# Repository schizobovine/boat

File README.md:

Battery Operated Arduino Thermometer (B.O.A.T.)
==============

Similar to Moteino/Anarduino, an Arduino-compatiblish uC board with onboard
RFM69CW, SMA edge connector, and i2c thermometer chip. Powered by CR2032
batter. No onboard voltage regulation, so don't plug into 5V unless you need a
doorstop (the ATMega will be fine, but the wireless card and thermometer are
only specced for 3.6V max).

Yes, there are many Arduino-based wireless sensor projects out there. Most use
2.4GHz radios, however, and that's getting to be an awful crowded band,
especially if one lives in an apartment building. To avoid making that even
worse, I choose to use one of the other ISM bands, specifically 433MHz. This is
normally used for stuff like garage door openers and the like. (Also military
radar, which makes for some hilarious anecdotes).

Anyway, I decided to build my own board for this, even if other designs exist
that are probably better in just about every way. But this one is my own
special snowflake. It even has a cow on it! (Don't judge me.)

Licensed under the Creative Commons Attribution-ShareAlike License
(CC-BY-SA-4.0)

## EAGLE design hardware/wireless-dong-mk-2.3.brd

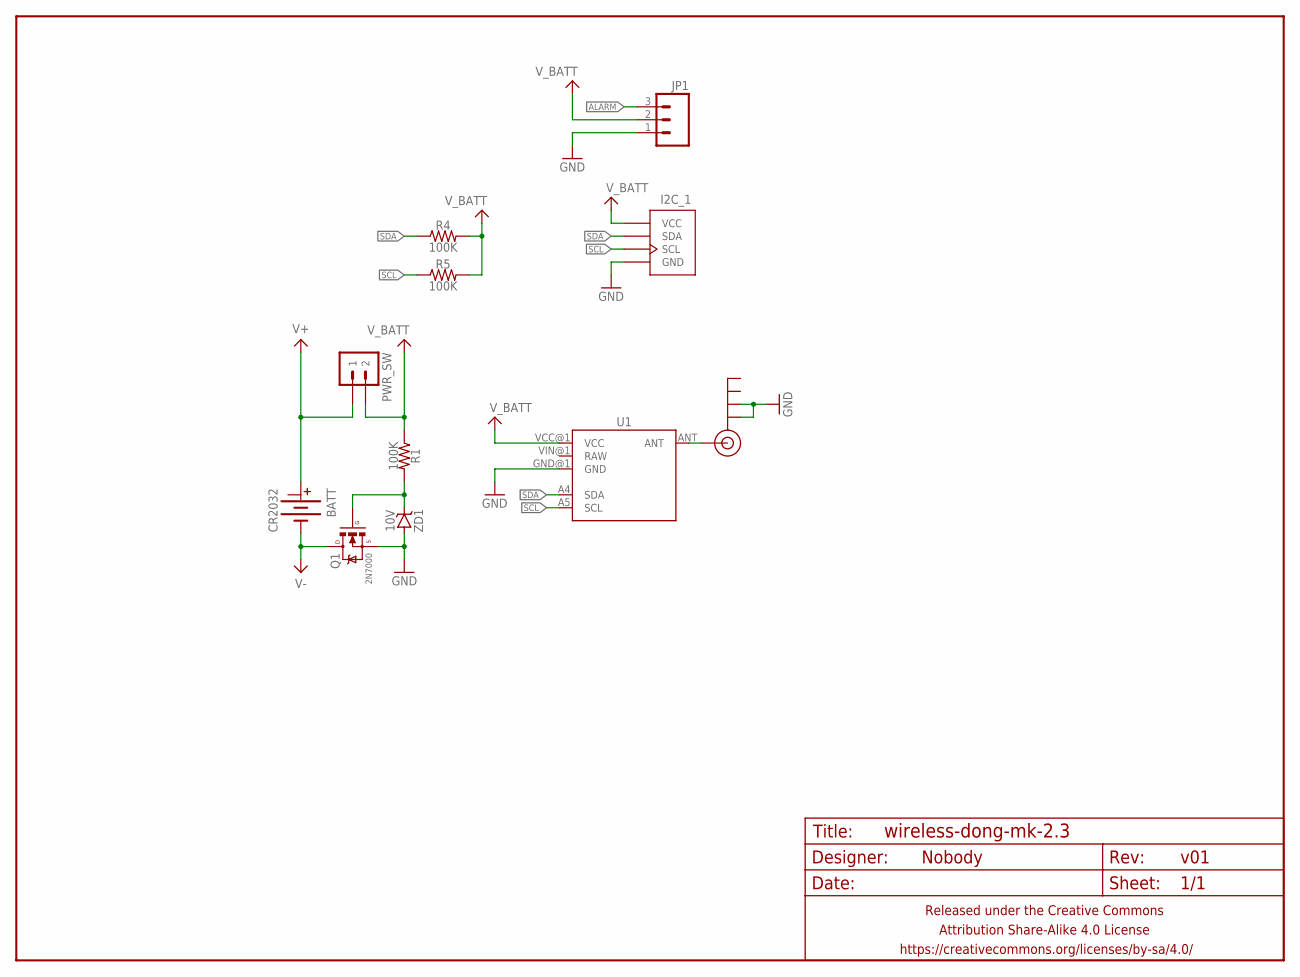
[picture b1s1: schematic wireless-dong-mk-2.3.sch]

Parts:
ANT: SMA_EDGE; SMA-EDGE
BATT: CR2032; BATTCON_20MM_MINE_STAHPIT
FRAME1: FRAME-LETTERNO_PACKAGE; DUMMY
I2C_1: M04-I2CJST-4-PH-RA-CENTERED; 1X04-JST-PH-RA-PTH-I2C-CENTERED
JP1: M03JST-PTH; JST-3-PH-RA-PTH
PWR_SW: M02PTH-CENTERED; 1X02-CENTER
Q1: 2N7000; SOT23
R1, R4, R5: 100K; R0805
U1: MOTEINO_BOAT
ZD1: 10V; SOT23

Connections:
ALARM: JP1.3
GND: ANT.GND@0 (GND), ANT.GND@1 (GND), I2C_1.1 (GND), JP1.1, Q1.2 (S), U1.GND@1 (GND), ZD1.1 (A), ZD1.2 (A)
unnamed: Q1.1 (G), R1.2, ZD1.3 (C)
unnamed: ANT.SIG (SIGNAL), U1.ANT
SCL: I2C_1.4 (SCL), R5.1, U1.A5 (SCL)
SDA: I2C_1.3 (SDA), R4.1, U1.A4 (SDA)
V+: BATT.TOP@1 (+), PWR_SW.1
V-: BATT.BOTTOM (-), Q1.3 (D)
V_BATT: I2C_1.2 (VCC), JP1.2, PWR_SW.2, R1.1, R4.2, R5.2, U1.VCC@1 (VCC)

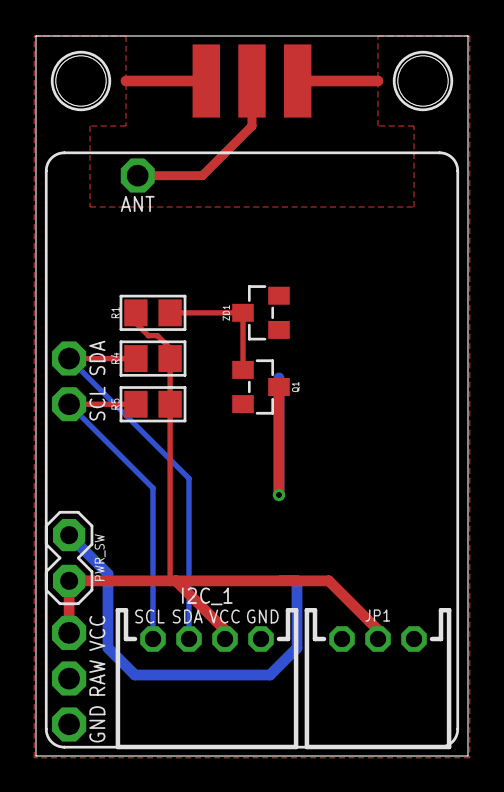
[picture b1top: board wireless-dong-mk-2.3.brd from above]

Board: 2 copper layers, 24.0 x 40.0 mm, 12 parts (1 on the bottom side), 8 nets.

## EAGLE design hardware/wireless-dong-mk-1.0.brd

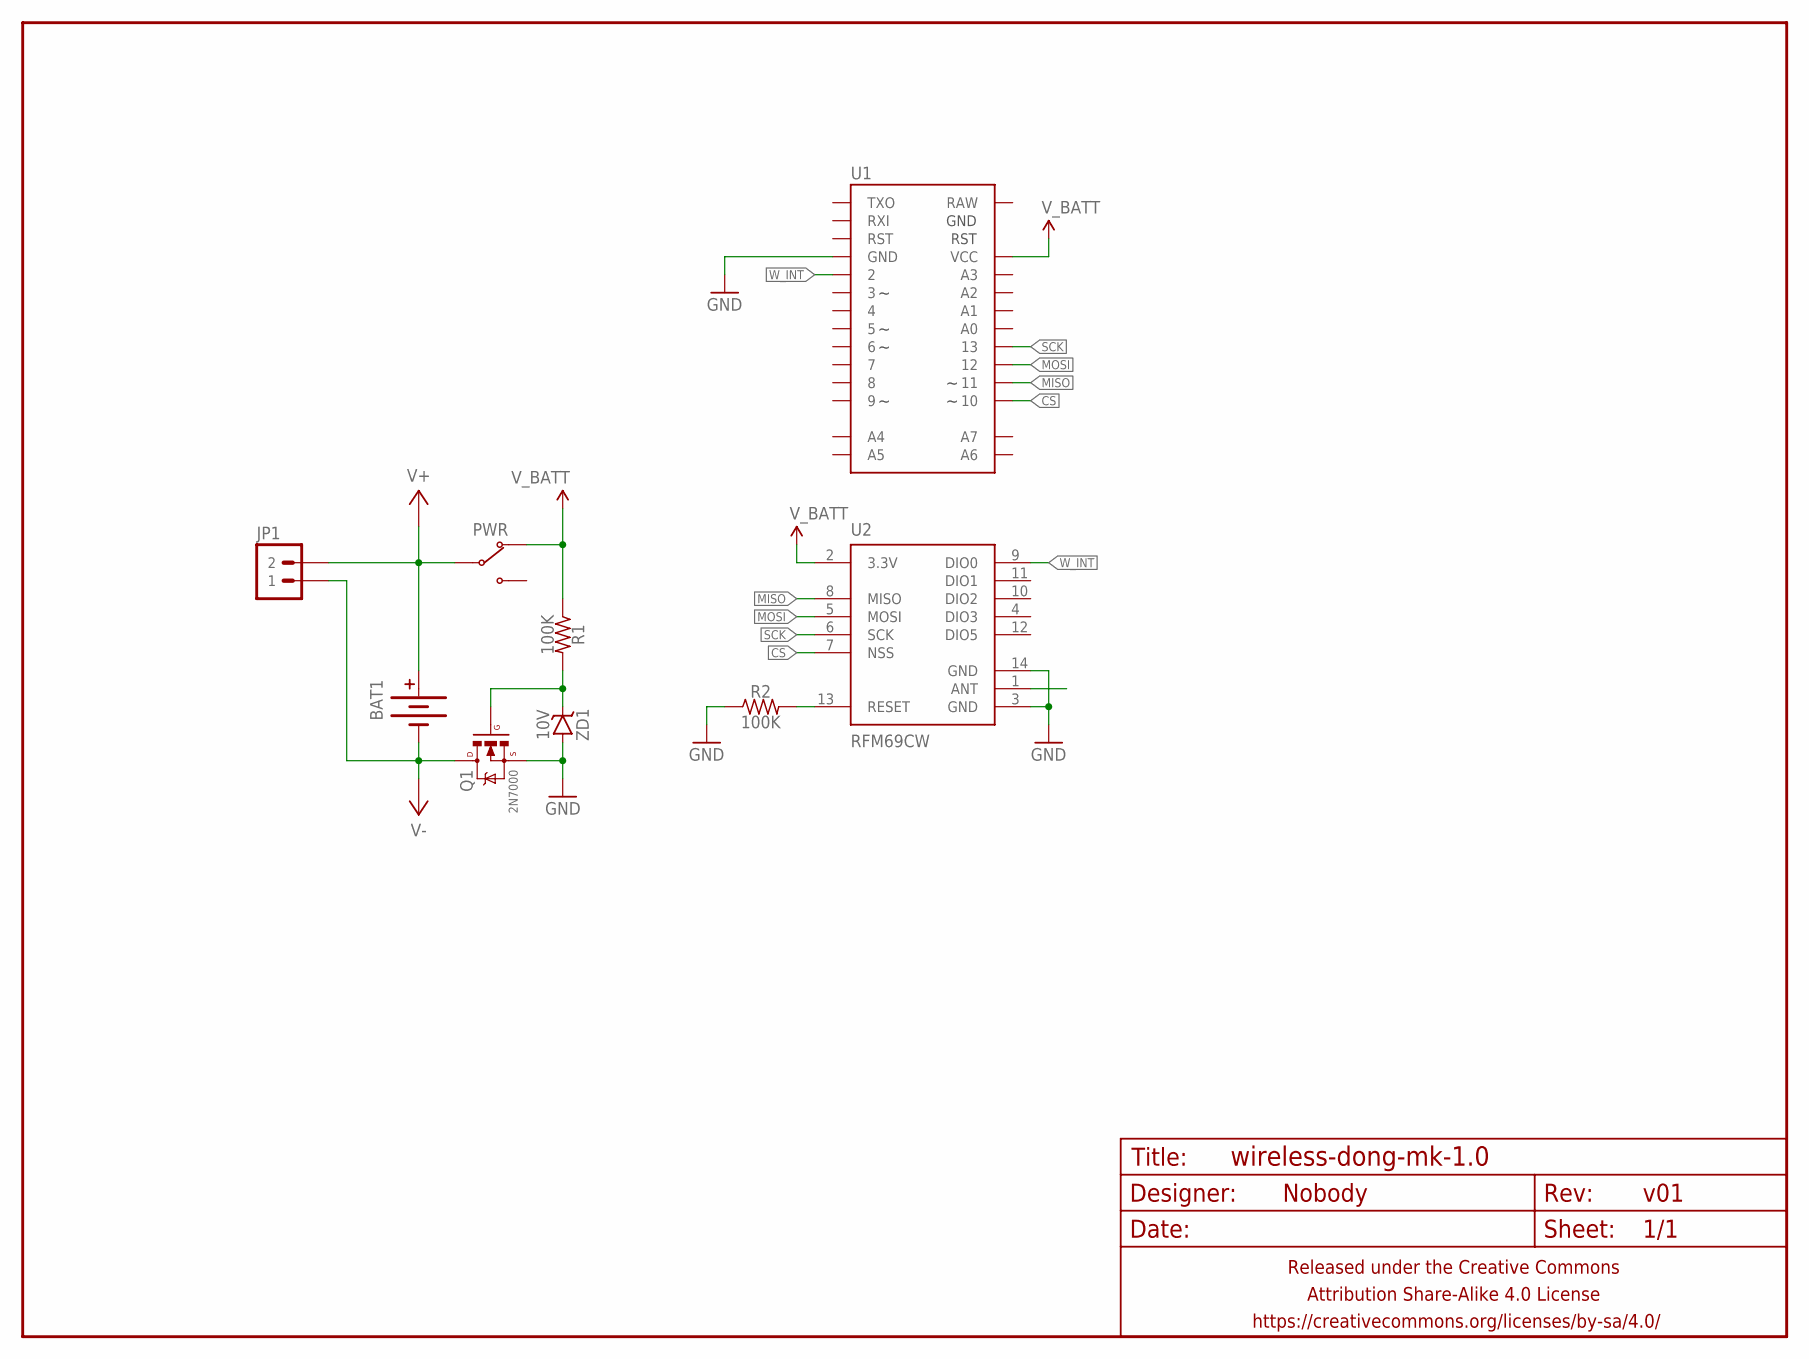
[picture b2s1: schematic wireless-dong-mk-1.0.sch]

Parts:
BAT1: BATTERYAA; BATTERY-AA
FRAME1: FRAME-LETTERNO_PACKAGE; DUMMY
JP1: M02PTH-CENTERED-R+; 1X02-CENTER-R+
PWR: SWITCH-SPDTPTH-RA-2.54MM; SPDT-RA-2.54MM
Q1: 2N7000; SOT23
R1, R2: 100K; R0603
U1: ARDUINO-PRO-MINI-NO-FTDIARDUINO_PRO_MINI_NO_FTDI_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; ARDUINO_PRO_MINI_NO_FTDI_NO_SILK
U2: RFM69CW; RFM69CW-XXXS2
ZD1: 10V; SOT23

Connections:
CS: U1.10, U2.7 (NSS)
GND: Q1.2 (S), R2.1, U1.GND@1 (GND), U1.GND@2 (GND), U2.3 (GND), U2.14 (GND), ZD1.1 (A), ZD1.2 (A)
MISO: U1.11, U2.8 (MISO)
MOSI: U1.12, U2.5 (MOSI)
unnamed: Q1.1 (G), R1.2, ZD1.3 (C)
unnamed: R2.2, U2.13 (RESET)
SCK: U1.13, U2.6 (SCK)
V+: BAT1.PWR@1 (+), BAT1.PWR@2 (+), JP1.2, PWR.2 (COM)
V-: BAT1.GND@1 (-), BAT1.GND@2 (-), JP1.1, Q1.3 (D)
V_BATT: PWR.1 (NC), R1.1, U1.VCC, U2.2 (3.3V)
W_INT: U1.2, U2.9 (DIO0)

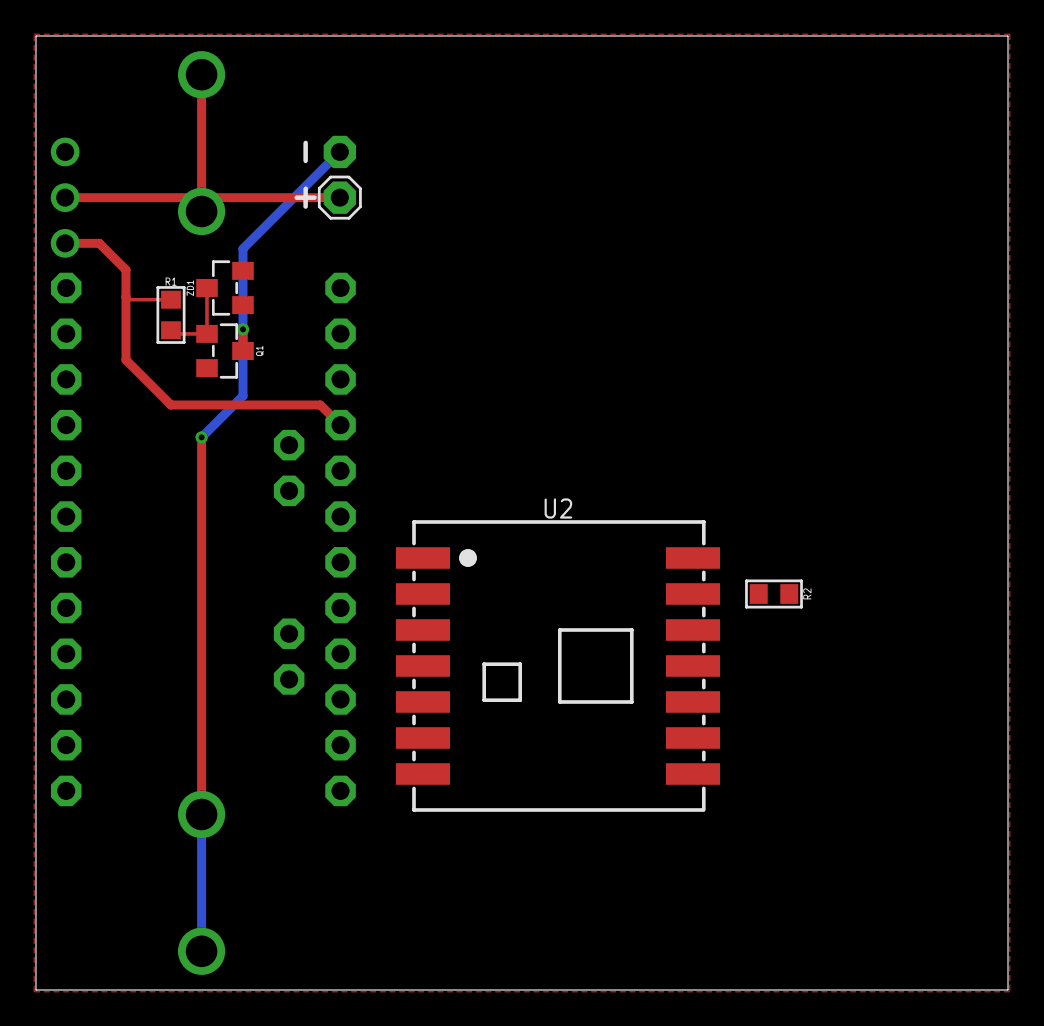
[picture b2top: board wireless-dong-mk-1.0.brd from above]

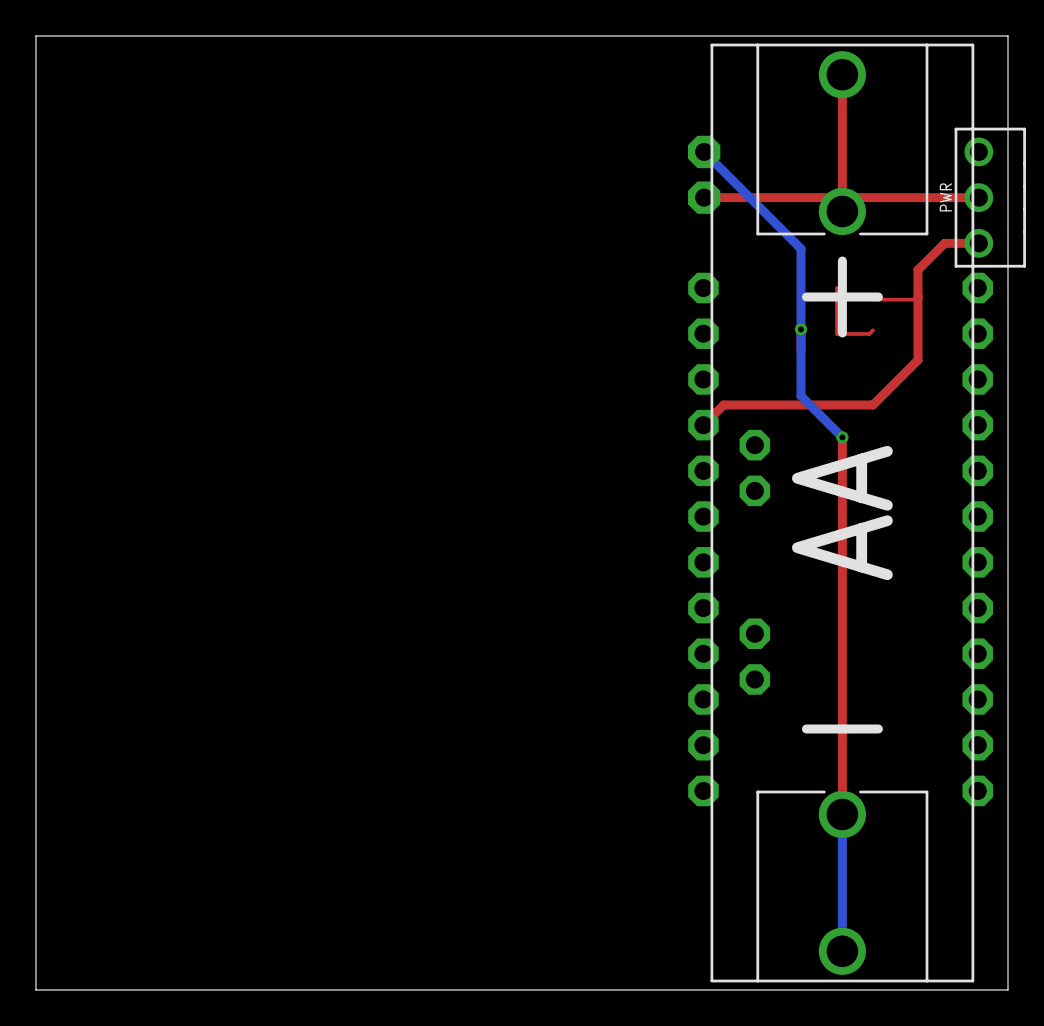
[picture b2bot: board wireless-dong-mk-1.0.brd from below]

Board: 2 copper layers, 54.0 x 53.0 mm, 10 parts (2 on the bottom side), 11 nets.

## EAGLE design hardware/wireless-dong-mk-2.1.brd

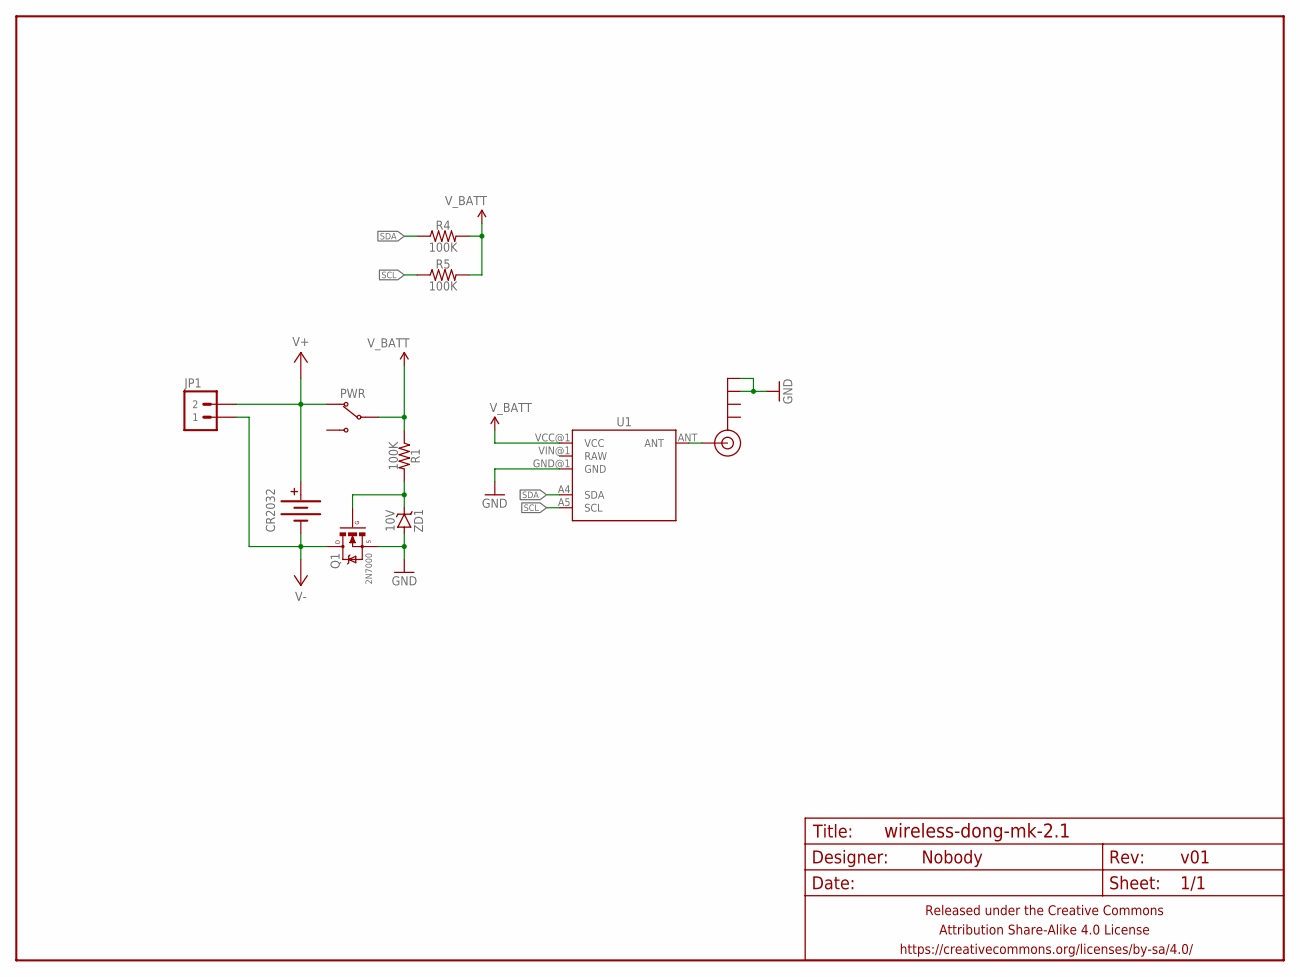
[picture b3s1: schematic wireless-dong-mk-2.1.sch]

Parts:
ANT: SMA_EDGE; SMA-EDGE
CR2032: BATTERY20PTH_TOPLOAD; BATTCON_20MM_PTH_TOPLOAD
FRAME1: FRAME-LETTERNO_PACKAGE; DUMMY
JP1: M02PTH-CENTERED-R+; 1X02-CENTER-R+
PWR: SWITCH-SPDTPTH-RA-2.54MM; SPDT-RA-2.54MM
Q1: 2N7000; SOT23
R1, R4, R5: 100K; R0603
U1: MOTEINO_BOAT
ZD1: 10V; SOT23

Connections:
GND: ANT.GND@2 (GND), ANT.GND@3 (GND), Q1.2 (S), U1.GND@1 (GND), ZD1.1 (A), ZD1.2 (A)
unnamed: Q1.1 (G), R1.2, ZD1.3 (C)
unnamed: ANT.SIG (SIGNAL), U1.ANT
SCL: R5.1, U1.A5 (SCL)
SDA: R4.1, U1.A4 (SDA)
V+: CR2032.+, JP1.2, PWR.1 (NC)
V-: CR2032.-, JP1.1, Q1.3 (D)
V_BATT: PWR.2 (COM), R1.1, R4.2, R5.2, U1.VCC@1 (VCC)

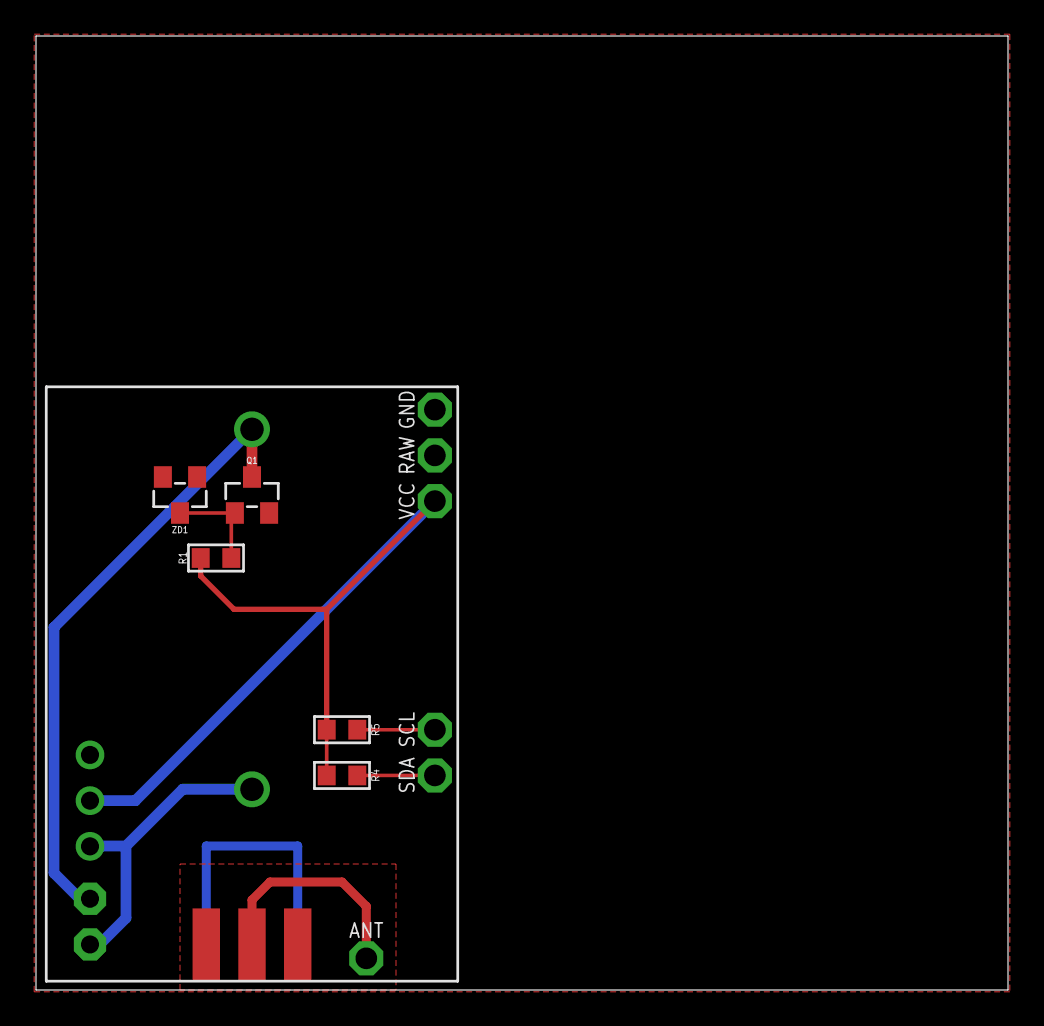
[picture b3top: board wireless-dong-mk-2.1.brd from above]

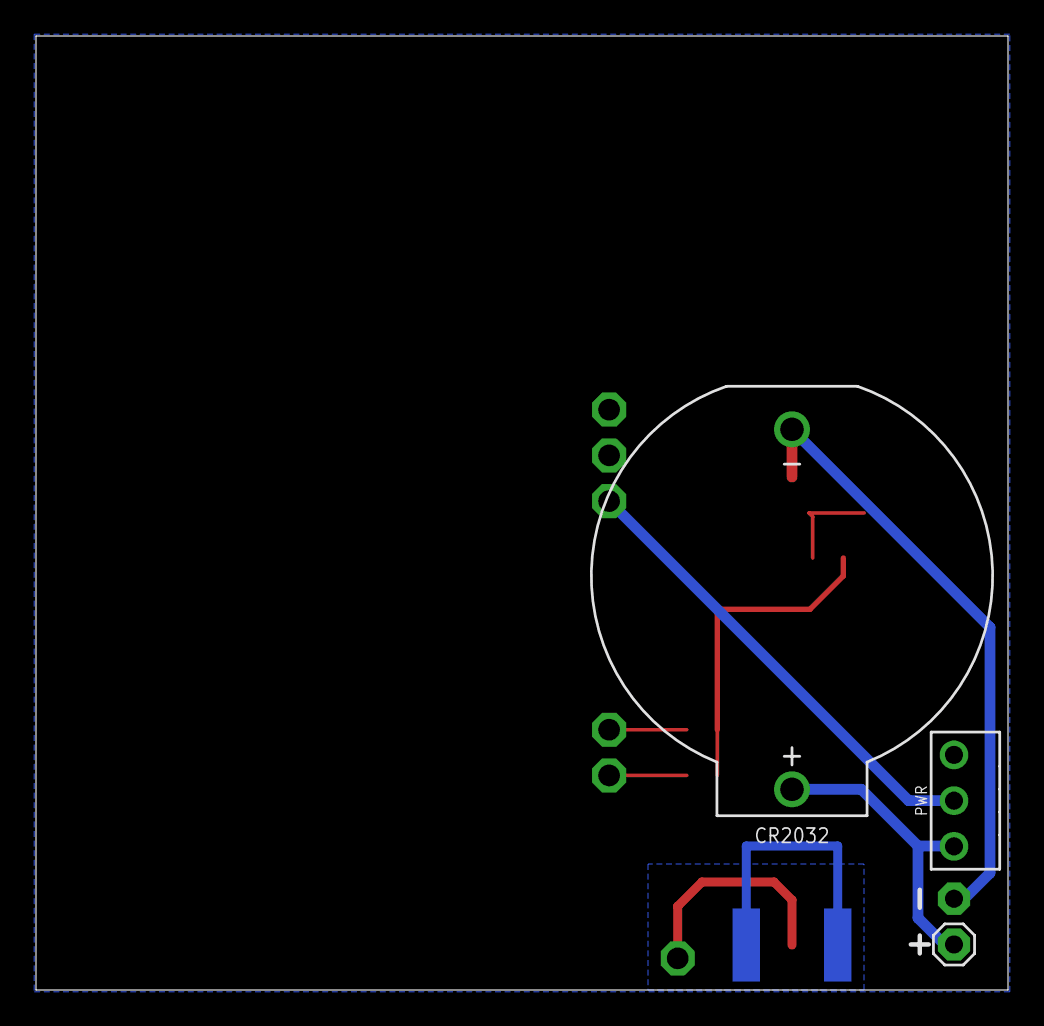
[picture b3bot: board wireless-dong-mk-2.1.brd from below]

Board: 2 copper layers, 54.0 x 53.0 mm, 11 parts (3 on the bottom side), 8 nets.

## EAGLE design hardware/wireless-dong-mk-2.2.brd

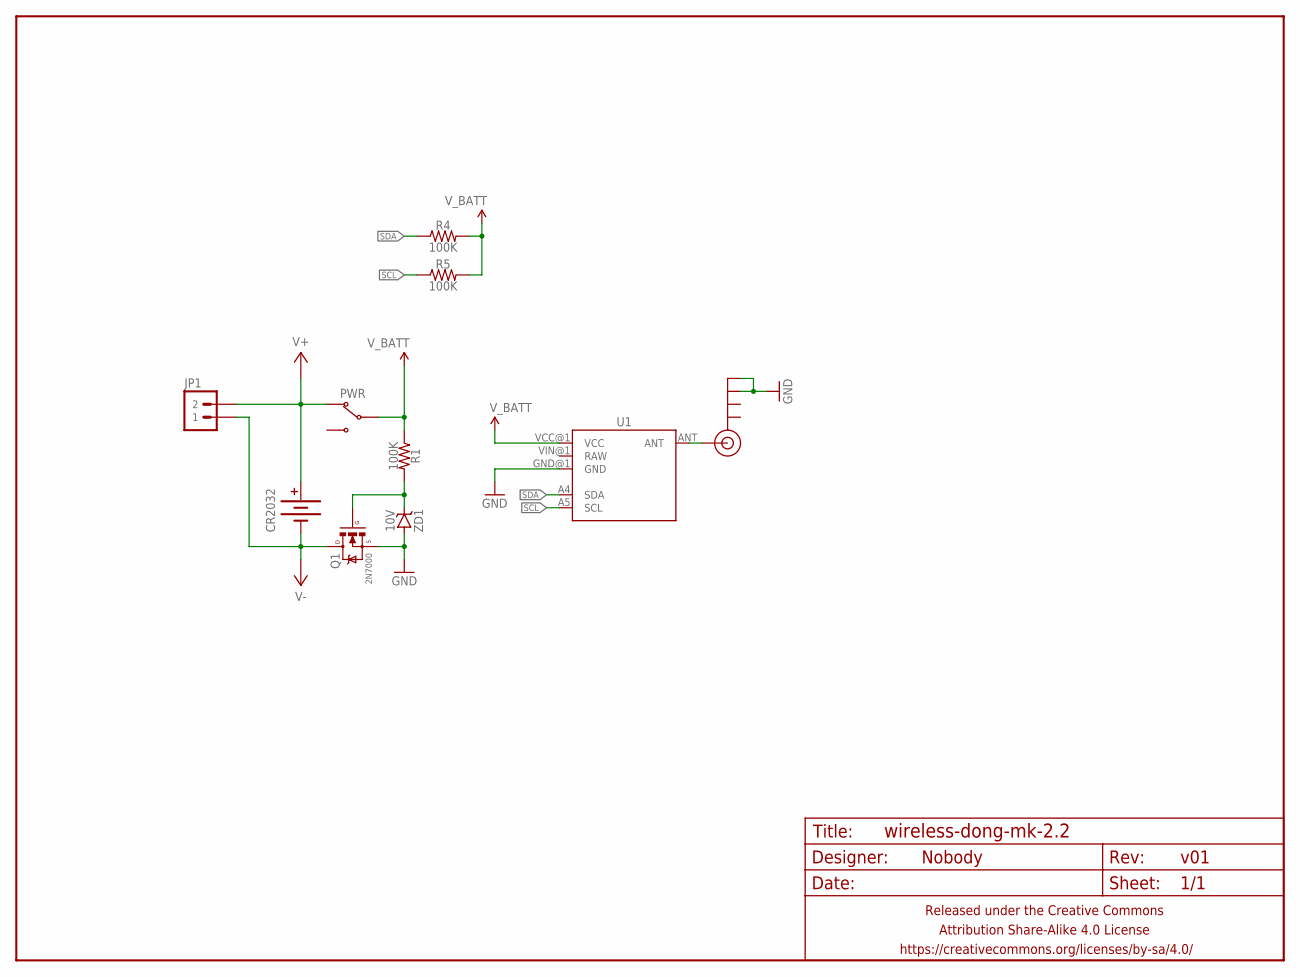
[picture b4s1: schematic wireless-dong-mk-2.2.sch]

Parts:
ANT: SMA_EDGE; SMA-EDGE
CR2032: BATTERY20PTH_TOPLOAD; BATTCON_20MM_PTH_TOPLOAD
FRAME1: FRAME-LETTERNO_PACKAGE; DUMMY
JP1: M02PTH-CENTERED-R+; 1X02-CENTER-R+
PWR: SWITCH-SPDTPTH-RA-2.54MM; SPDT-RA-2.54MM
Q1: 2N7000; TO-92-AMMO
R1, R4, R5: 100K; RESISTOR-AXIAL-PTH-7.62MM
U1: MOTEINO_BOAT
ZD1: 10V; DIODE-ZENNER-7.62MM

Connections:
GND: ANT.GND@2 (GND), ANT.GND@3 (GND), Q1.1 (S), U1.GND@1 (GND), ZD1.A
unnamed: Q1.2 (G), R1.P$2 (2), ZD1.K (C)
unnamed: ANT.SIG (SIGNAL), U1.ANT
SCL: R5.P$1 (1), U1.A5 (SCL)
SDA: R4.P$1 (1), U1.A4 (SDA)
V+: CR2032.+, JP1.2, PWR.1 (NC)
V-: CR2032.-, JP1.1, Q1.3 (D)
V_BATT: PWR.2 (COM), R1.P$1 (1), R4.P$2 (2), R5.P$2 (2), U1.VCC@1 (VCC)

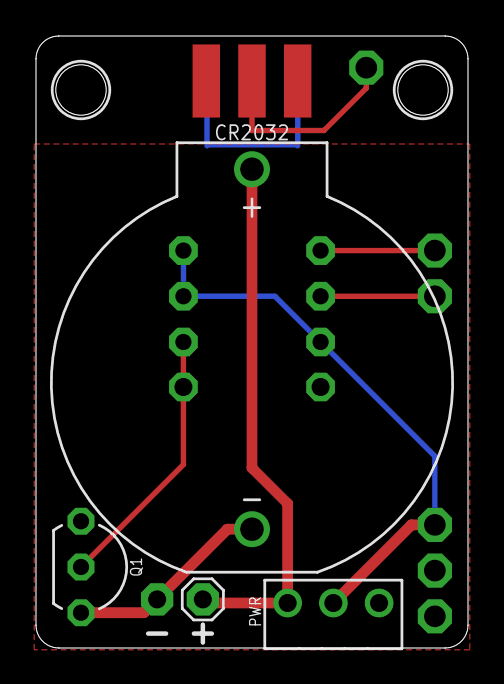
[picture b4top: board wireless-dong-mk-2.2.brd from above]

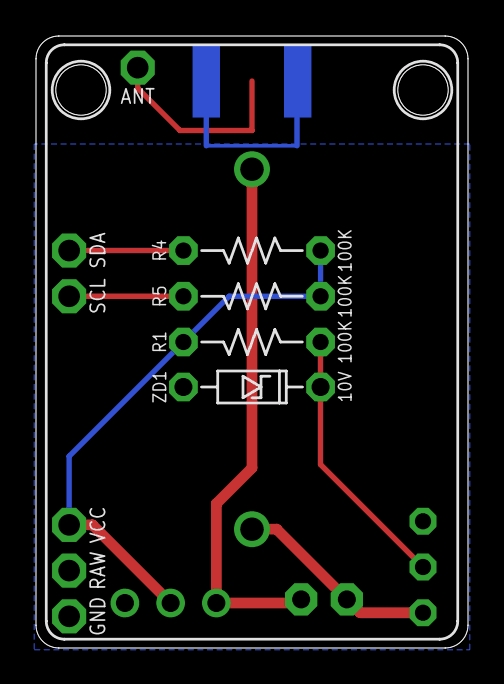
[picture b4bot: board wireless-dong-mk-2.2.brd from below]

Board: 2 copper layers, 24.0 x 34.0 mm, 11 parts (5 on the bottom side), 8 nets.

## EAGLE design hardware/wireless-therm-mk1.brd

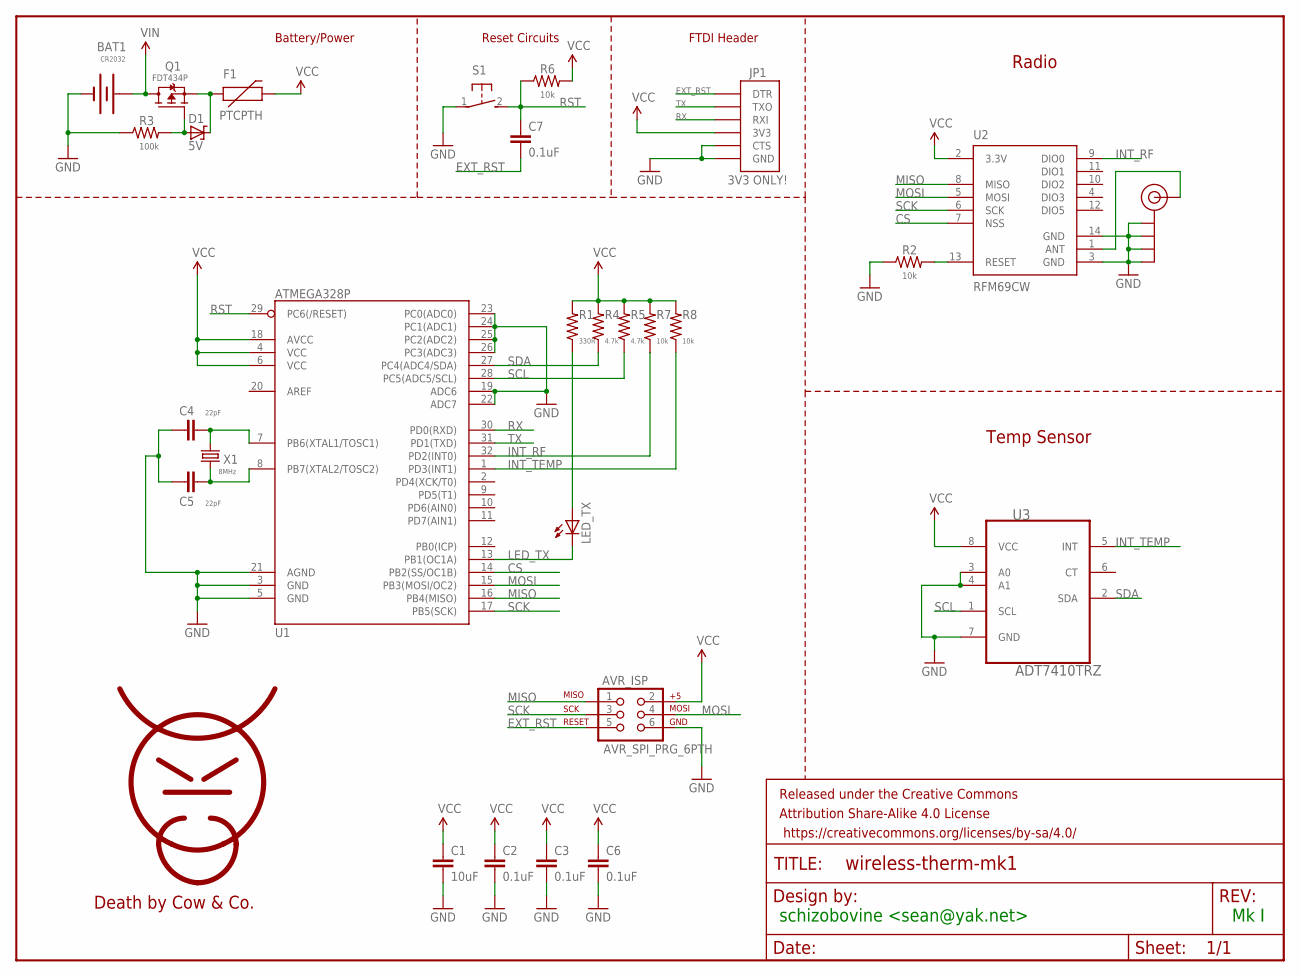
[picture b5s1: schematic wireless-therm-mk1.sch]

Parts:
AVR_ISP: AVR_SPI_PRG_6PTH; 2X3
BAT1: CR2032; BATTCON_20MM
C1: 10uF; C050-025X075
C2, C3, C6, C7: 0.1uF; C025-024X044
C4, C5: 22pF; C025-025X050
D1: 5V; DO34Z7
F1: PTCPTH; PTC
FRAME1: FRAME-LETTER; CREATIVE_COMMONS
JP1: 3V3 ONLY!; FTDI_3V3
LED_TX: GREEN; LED3MM
Q1: FDT434P; SOT223
R1: 330R; 0204/5
R2, R6, R7, R8: 10k; 0204/5
R3: 100k; 0204/5
R4, R5: 4.7k; 0204/5
S1: DTS-3
SMA_CON: SMA_EDGE; SMA-EDGE
U1: ATMEGA328P; TQFP32-08
U2: RFM69CW; RFM69CW-XXXS2
U3: ADT7410TRZ; SOIC127P600X175-8N
U$4: COW
X1: 8MHz; HC49U70

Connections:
ANT: SMA_CON.SIG (SIGNAL), U2.1 (ANT)
CS: U1.14 (PB2(SS/OC1B)), U2.7 (NSS)
EXT_RST: AVR_ISP.5, C7.2, JP1.P$1 (DTR)
GND: AVR_ISP.6, BAT1.2 (-), C1.2, C2.2, C3.2, C4.1, C5.1, C6.2, JP1.P$5 (CTS), JP1.P$6 (GND), R2.1, R3.1, S1.1, SMA_CON.GND@0 (GND), SMA_CON.GND@1 (GND), SMA_CON.GND@2 (GND), SMA_CON.GND@3 (GND), U1.3 (GND), U1.5 (GND), U1.19 (ADC6), U1.21 (AGND), U1.22 (ADC7), U1.23 (PC0(ADC0)), U1.24 (PC1(ADC1)), U1.25 (PC2(ADC2)), U1.26 (PC3(ADC3)), U2.3 (GND), U2.14 (GND), U3.3 (A0), U3.4 (A1), U3.7 (GND)
INT_RF: R7.1, U1.32 (PD2(INT0)), U2.9 (DIO0)
INT_TEMP: R8.1, U1.1 (PD3(INT1)), U3.5 (INT)
LED_TX: LED_TX.K (C), U1.13 (PB1(OC1A))
MISO: AVR_ISP.1, U1.16 (PB4(MISO)), U2.8 (MISO)
MOSI: AVR_ISP.4, U1.15 (PB3(MOSI/OC2)), U2.5 (MOSI)
unnamed: LED_TX.A, R1.1
unnamed: R2.2, U2.13 (RESET)
unnamed: D1.C, F1.P$1 (1), Q1.3 (S)
unnamed: C4.2, U1.7 (PB6(XTAL1/TOSC1)), X1.2
unnamed: C5.2, U1.8 (PB7(XTAL2/TOSC2)), X1.1
unnamed: D1.A, Q1.1 (G), R3.2
RST: C7.1, R6.1, S1.2, U1.29 (PC6(/RESET))
RX: JP1.P$3 (RXI), U1.30 (PD0(RXD))
SCK: AVR_ISP.3, U1.17 (PB5(SCK)), U2.6 (SCK)
SCL: R5.1, U1.28 (PC5(ADC5/SCL)), U3.1 (SCL)
SDA: R4.1, U1.27 (PC4(ADC4/SDA)), U3.2 (SDA)
TX: JP1.P$2 (TXO), U1.31 (PD1(TXD))
VCC: AVR_ISP.2, C1.1, C2.1, C3.1, C6.1, F1.P$2 (2), JP1.P$4 (3V3), R1.2, R4.2, R5.2, R6.2, R7.2, R8.2, U1.4 (VCC), U1.6 (VCC), U1.18 (AVCC), U2.2 (3.3V), U3.8 (VCC)
VIN: BAT1.1 (+), BAT1.3 (+), Q1.2 (D), Q1.4 (D)

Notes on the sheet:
schizobovine <sean@yak.net>
Mk I
Battery/Power
Reset Circuits
FTDI Header
Radio
Temp Sensor

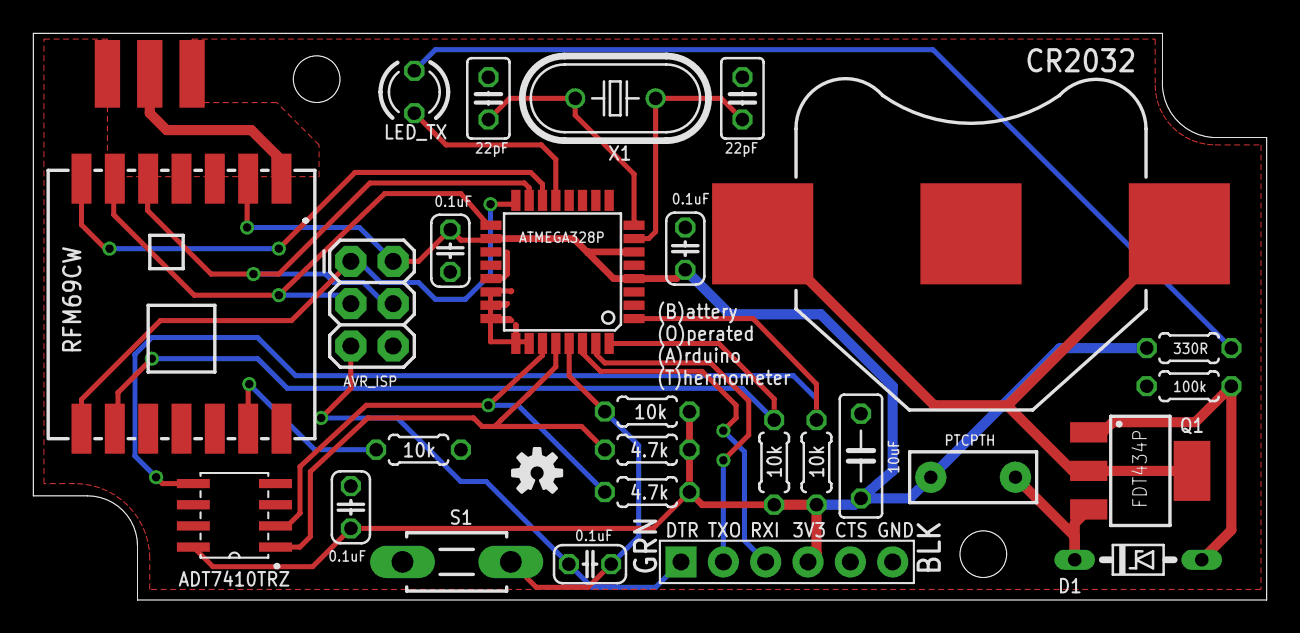
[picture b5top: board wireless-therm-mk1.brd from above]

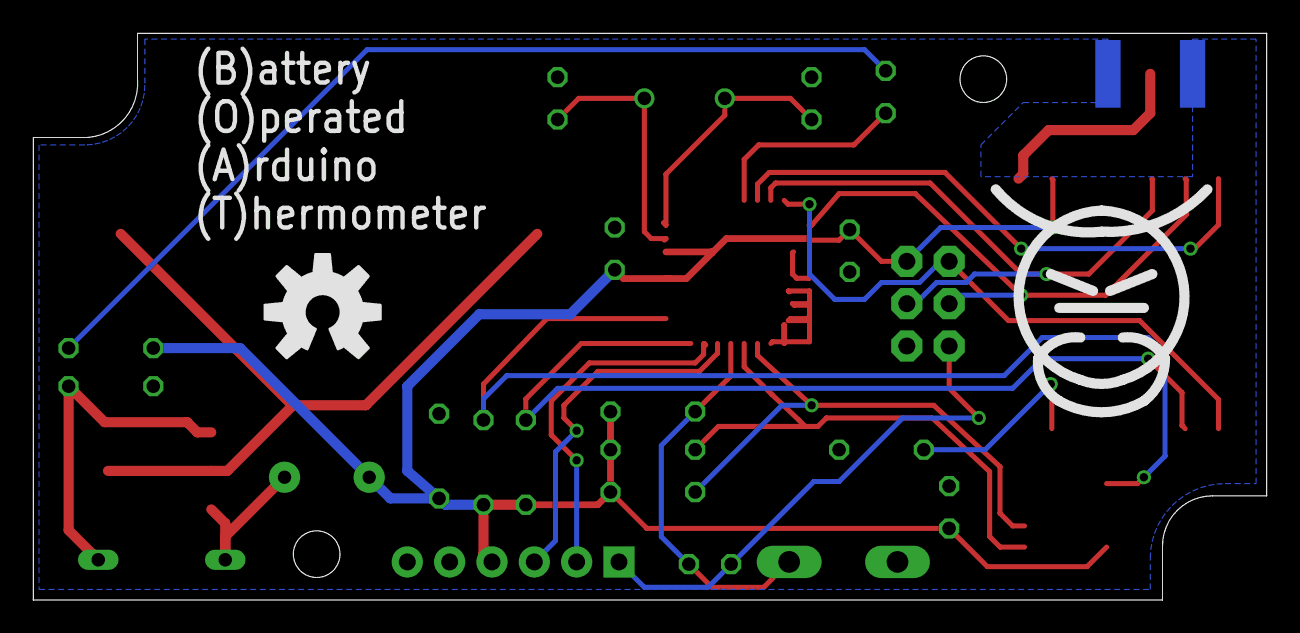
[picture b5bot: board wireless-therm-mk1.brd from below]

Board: 2 copper layers, 74.0 x 34.0 mm, 32 parts (2 on the bottom side), 23 nets.

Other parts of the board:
LOGO1: OSHW-LOGOS; OSHW-LOGO-S
U$3: OSHW-LOGO-L

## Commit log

2014-10-09 standardizedish ignore file for both C and Eagle files
2015-05-26 wireless dongles

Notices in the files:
parts and their libraries:
A_butts: Released under the Creative Commons Attribution Share-Alike 4.0 License
A_butts: https://creativecommons.org/licenses/by-sa/4.0
A_butts: Released under the Creative Commons
